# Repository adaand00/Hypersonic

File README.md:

# Hypersonic
Platform for audio development with ESP32-S3, Work in progress.

Design goals: 
Modularity. Flexibility. High Fidelity. 

Based on previous project: [Supersonic Quantumbox](https://github.com/GustavAbrahamsson/Supersonic-Quantumbox)

## Development progress:

### Hardware
- [x] ESP32-s3 + CODEC module ([`/Hypersonic_pcb`](./Hypersonic_pcb/))
- [x] Pedal with screen, potentiometers, and connetors. ([`/Hypersonic_pedal_pcb`](./Hypersonic_pedal_pcb/))
- [x] Assembled
- [ ] Fully tested

### Software
- [x] Peripheral drivers
- [ ] FreeRTOS system
- [ ] User interface

### Effects

- [x] Saturation (Overdrive/Fuzz)
- [x] VU meter
- [ ] Linear filters
- [ ] Compression
- [ ] Rotary speaker
- [ ] Wah-wah
- [ ] Echo/Reverb

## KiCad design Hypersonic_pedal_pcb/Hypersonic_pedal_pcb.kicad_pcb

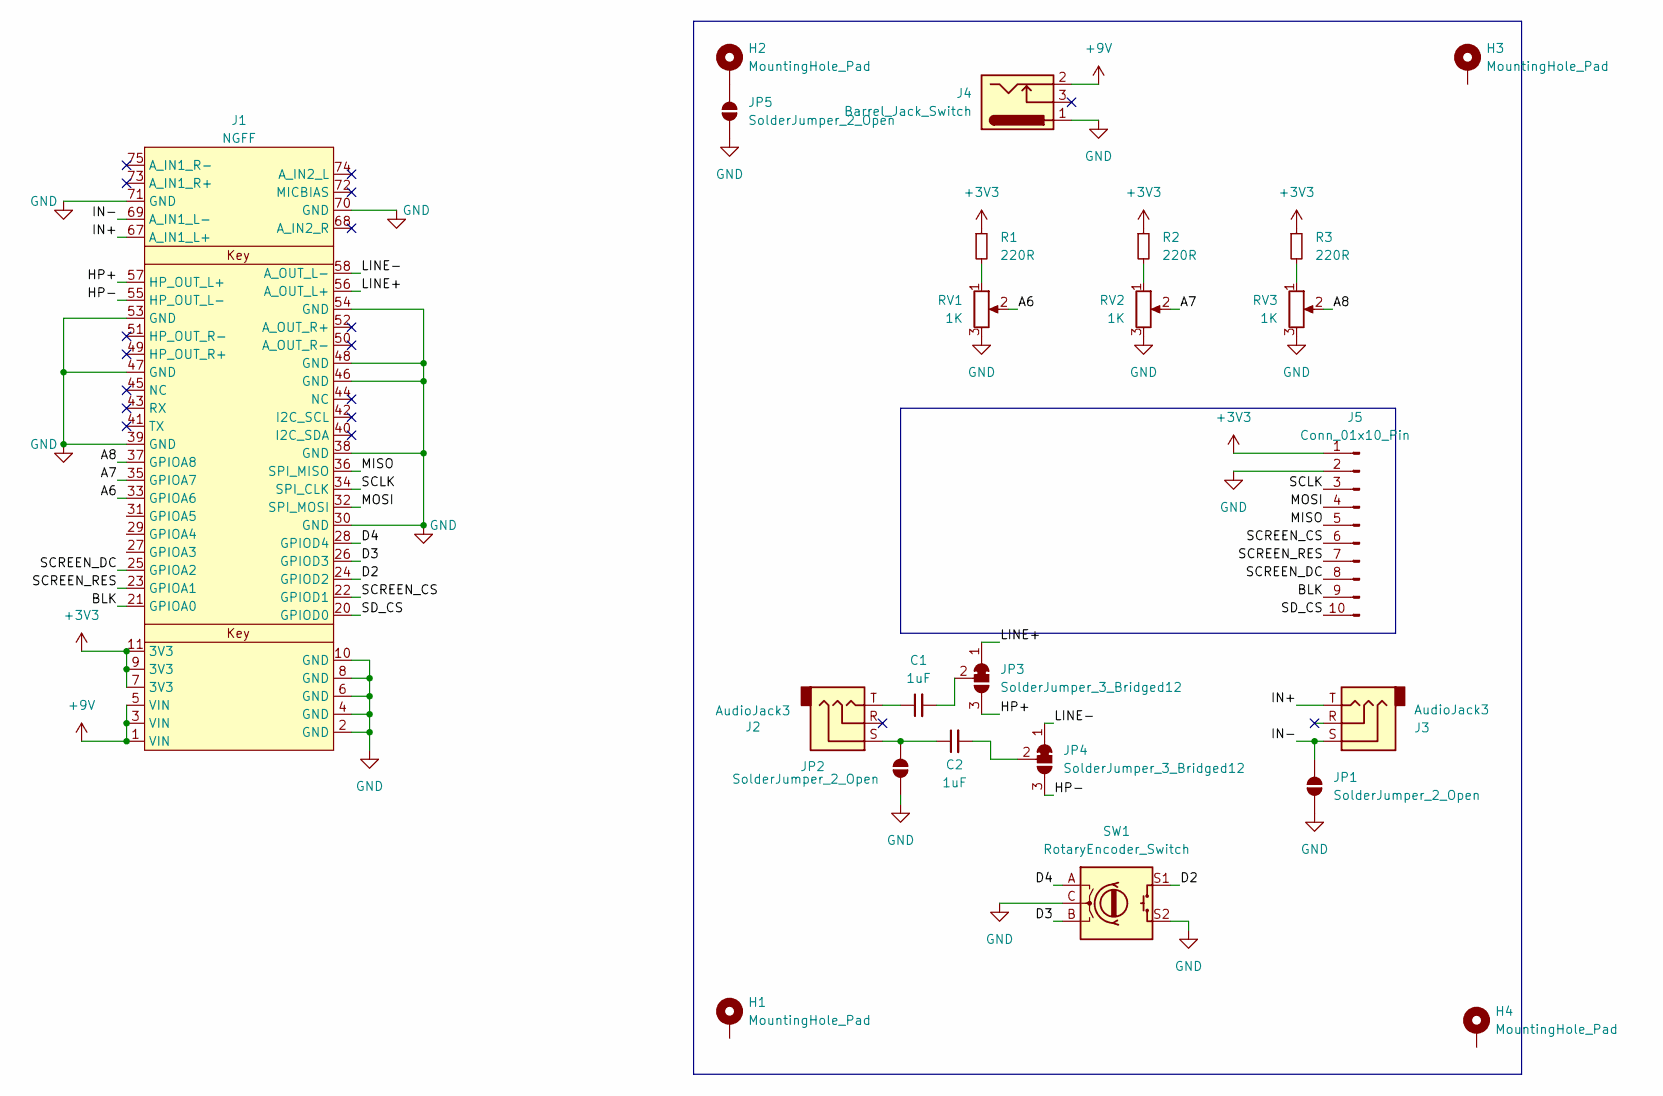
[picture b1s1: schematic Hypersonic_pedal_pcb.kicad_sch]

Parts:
C1, C2: 1uF; C_Rect_L18.0mm_W8.0mm_P15.00mm_FKS3_FKP3
H1, H2, H3, H4: MountingHole_Pad; MountingHole_2.2mm_M2_Pad_Via
J1: NGFF; TE_2199119-1
J2, J3: AudioJack3; Jack_6.35mm_Neutrik_NRJ6HF_Horizontal
J4: Barrel_Jack_Switch; BarrelJack_Horizontal
J5: Conn_01x10_Pin; DFROBOT_TFT_1_8
JP1, JP2, JP5: SolderJumper_2_Open; SolderJumper-2_P1.3mm_Open_TrianglePad1.0x1.5mm
JP3, JP4: SolderJumper_3_Bridged12; SolderJumper-3_P1.3mm_Bridged12_RoundedPad1.0x1.5mm
R1, R2, R3: 220R; R_0603_1608Metric
RV1, RV2, RV3: 1K; Potentiometer_Bourns_PTV09A-1_Single_Vertical
SW1: RotaryEncoder_Switch; RotaryEncoder_Bourns_Vertical_PEC12R-3x17F-Sxxxx

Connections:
+3V3: J1.7 (3V3), J1.9 (3V3), J1.11 (3V3), J5.1, R1.1, R2.1, R3.1
+9V: J1.1 (VIN), J1.3 (VIN), J1.5 (VIN), J4.2
/A6: J1.33 (GPIOA6), RV1.2
/A7: J1.35 (GPIOA7), RV2.2
/A8: J1.37 (GPIOA8), RV3.2
/BLK: J1.21 (GPIOA0), J5.9
/D2: J1.24 (GPIOD2), SW1.S1
/D3: J1.26 (GPIOD3), SW1.B
/D4: J1.28 (GPIOD4), SW1.A
/HP+: J1.57 (HP_OUT_L+), JP3.3 (B)
/HP-: J1.55 (HP_OUT_L-), JP4.3 (B)
/IN+: J1.67 (A_IN1_L+), J3.T
/IN-: J1.69 (A_IN1_L-), J3.S, JP1.2 (B)
/LINE+: J1.56 (A_OUT_L+), JP3.1 (A)
/LINE-: J1.58 (A_OUT_L-), JP4.1 (A)
/MISO: J1.36 (SPI_MISO), J5.5
/MOSI: J1.32 (SPI_MOSI), J5.4
/SCLK: J1.34 (SPI_CLK), J5.3
/SCREEN_CS: J1.22 (GPIOD1), J5.6
/SCREEN_DC: J1.25 (GPIOA2), J5.8
/SCREEN_RES: J1.23 (GPIOA1), J5.7
/SD_CS: J1.20 (GPIOD0), J5.10
GND: J1.2 (GND), J1.4 (GND), J1.6 (GND), J1.8 (GND), J1.10 (GND), J1.30 (GND), J1.38 (GND), J1.39 (GND), J1.46 (GND), J1.47 (GND), J1.48 (GND), J1.53 (GND), J1.54 (GND), J1.70 (GND), J1.71 (GND), J4.1, J5.2, JP1.1 (A), JP2.1 (A), JP5.1 (A), RV1.3, RV2.3, RV3.3, SW1.C, SW1.S2
unnamed: C1.1, J2.T
unnamed: C2.1, J2.S, JP2.2 (B)
unnamed: C1.2, JP3.2 (C)
unnamed: C2.2, JP4.2 (C)
unnamed: H2.1, JP5.2 (B)
unnamed: R1.2, RV1.1
unnamed: R2.2, RV2.1
unnamed: R3.2, RV3.1

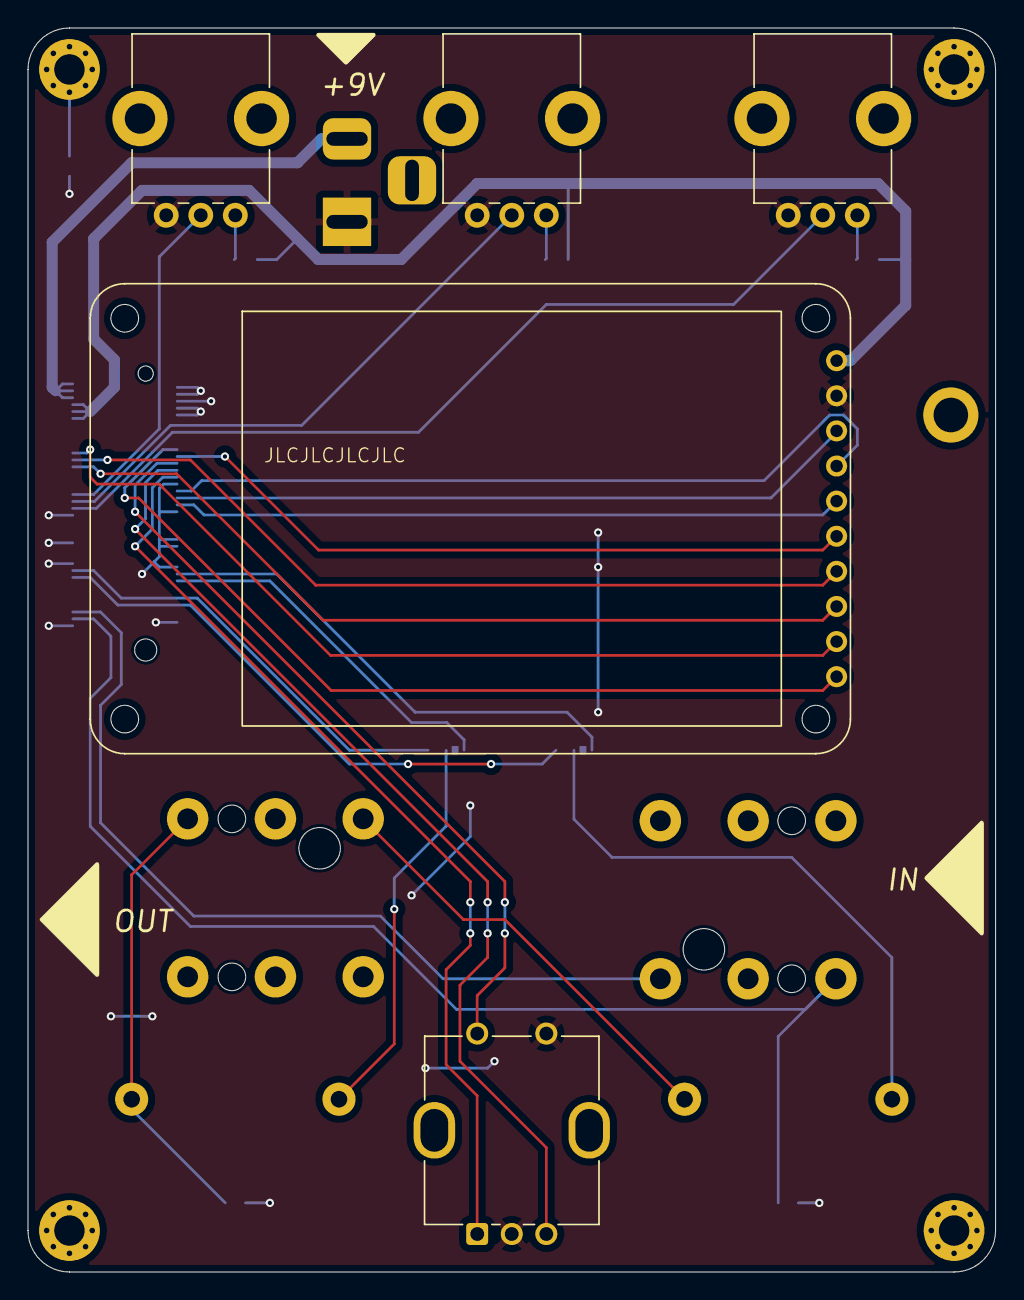
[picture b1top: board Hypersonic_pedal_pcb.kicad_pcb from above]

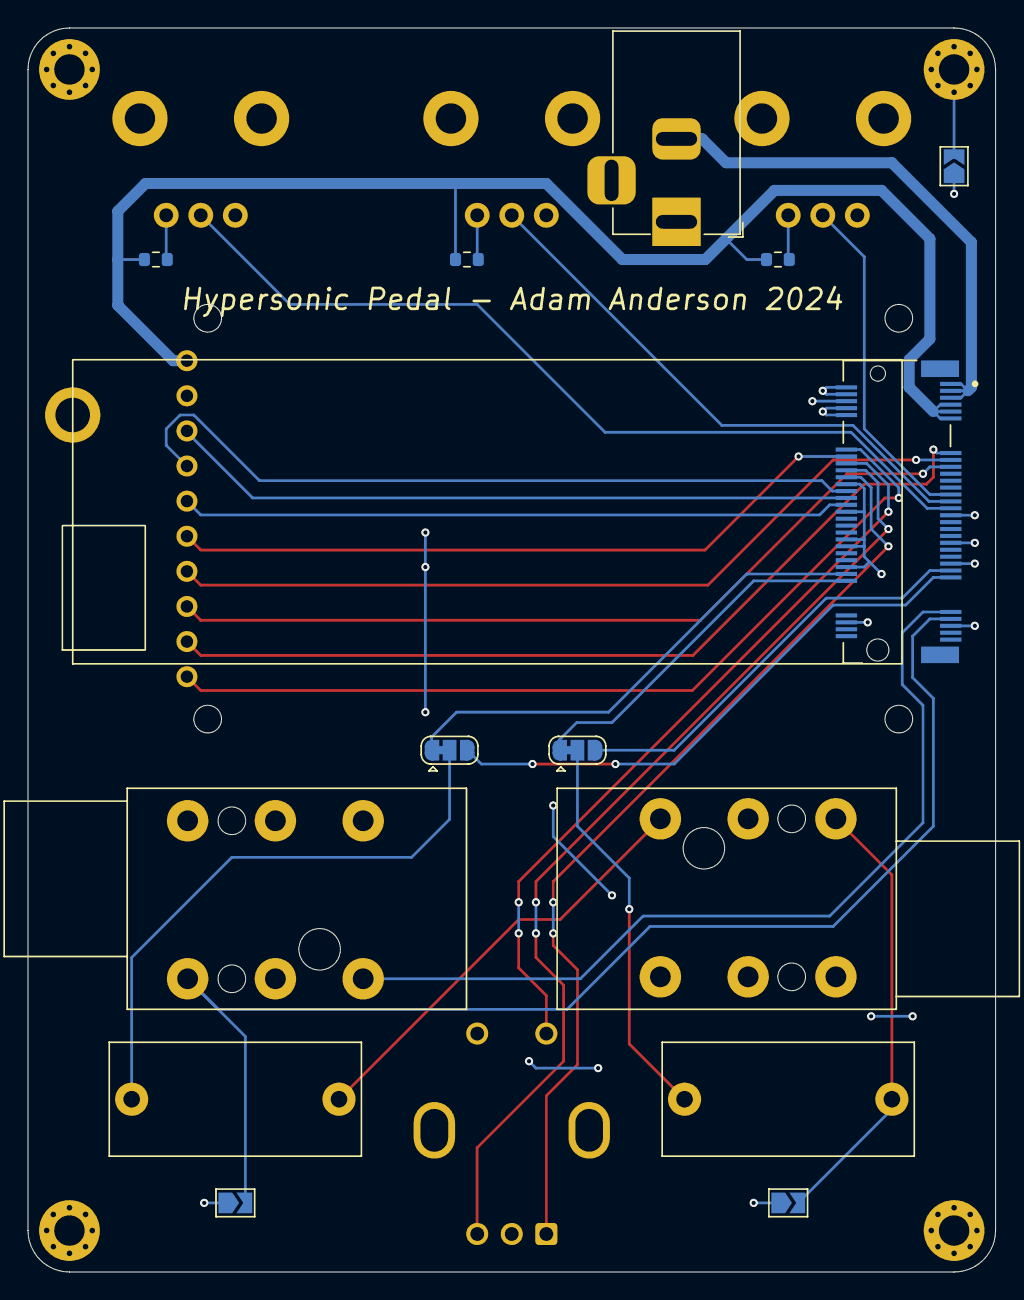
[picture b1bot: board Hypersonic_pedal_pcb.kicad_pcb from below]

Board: 2 copper layers, 70.0 x 90.0 mm, 23 parts (14 on the bottom side), 31 nets.

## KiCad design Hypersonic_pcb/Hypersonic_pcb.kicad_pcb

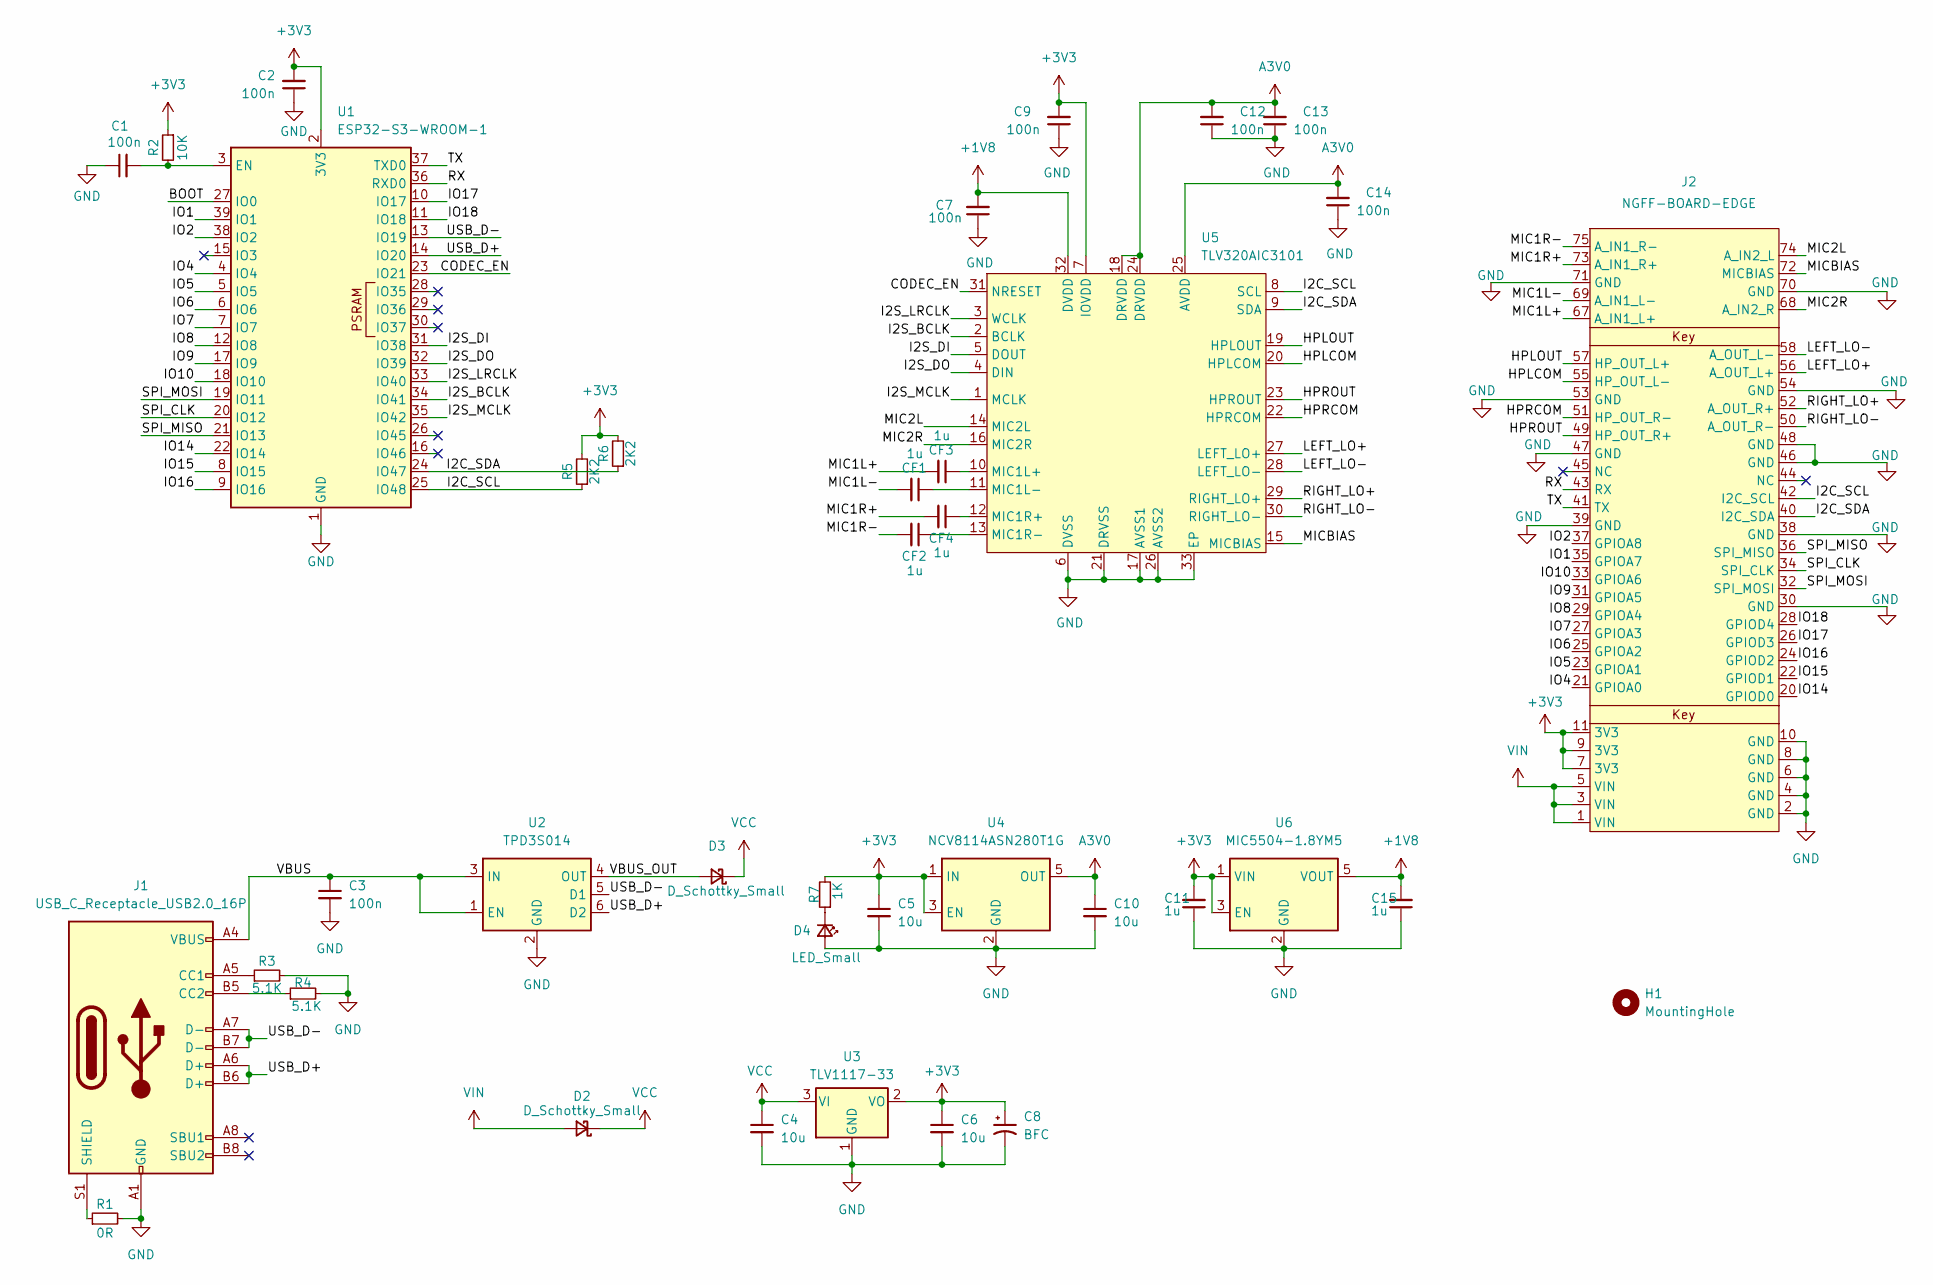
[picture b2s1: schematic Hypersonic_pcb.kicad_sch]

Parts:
C1, C2, C3, C7, C9, C12, C13, C14: 100n; C_0402_1005Metric
C4, C5, C6, C10: 10u; C_0805_2012Metric
C8: BFC; C_Elec_6.3x5.8
C11, C15: 1u; C_0603_1608Metric
CF1, CF2, CF3, CF4: 1u; C_1210_3225Metric
D2, D3: D_Schottky_Small; D_SOD-323_HandSoldering
D4: LED_Small; LED_0603_1608Metric
H1: MountingHole; MountingHole_2.2mm_M2
J1: USB_C_Receptacle_USB2.0_16P; USB_C_Receptacle_HRO_TYPE-C-31-M-12
J2: NGFF-BOARD-EDGE; NGFF_B+M
R1: 0R; R_0402_1005Metric
R2: 10K; R_0402_1005Metric
R3, R4: 5.1K; R_0402_1005Metric
R5, R6: 2K2; R_0402_1005Metric
R7: 1K; R_0402_1005Metric
U1: ESP32-S3-WROOM-1; ESP32-S3-WROOM-1U
U2: TPD3S014; SOT-23-6
U3: TLV1117-33; SOT-223-3_TabPin2
U4: NCV8114ASN280T1G; TSOT-23-5
U5: TLV320AIC3101; QFN-32-1EP_5x5mm_P0.5mm_EP3.45x3.45mm
U6: MIC5504-1.8YM5; SOT-23-5

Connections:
+1V8: C7.2, C15.2, U5.32 (DVDD), U6.5 (VOUT)
+3V3: C2.2, C5.1, C6.1, C8.1, C9.2, C11.2, J2.7 (3V3), J2.9 (3V3), J2.11 (3V3), R2.1, R5.2, R6.2, R7.2, U1.2 (3V3), U3.2 (VO), U4.1 (IN), U4.3 (EN), U5.7 (IOVDD), U6.1 (VIN), U6.3 (EN)
/BOOT: U1.27 (IO0)
/CODEC_EN: U1.23 (IO21), U5.31 (NRESET)
/HPLCOM: J2.55 (HP_OUT_L-), U5.20 (HPLCOM)
/HPLOUT: J2.57 (HP_OUT_L+), U5.19 (HPLOUT)
/HPRCOM: J2.51 (HP_OUT_R-), U5.22 (HPRCOM)
/HPROUT: J2.49 (HP_OUT_R+), U5.23 (HPROUT)
/I2C_SCL: J2.42 (I2C_SCL), R5.1, U1.25 (IO48), U5.8 (SCL)
/I2C_SDA: J2.40 (I2C_SDA), R6.1, U1.24 (IO47), U5.9 (SDA)
/I2S_BCLK: U1.34 (IO41), U5.2 (BCLK)
/I2S_DI: U1.31 (IO38), U5.5 (DOUT)
/I2S_DO: U1.32 (IO39), U5.4 (DIN)
/I2S_LRCLK: U1.33 (IO40), U5.3 (WCLK)
/I2S_MCLK: U1.35 (IO42), U5.1 (MCLK)
/IO1: J2.35 (GPIOA7), U1.39 (IO1)
/IO2: J2.37 (GPIOA8), U1.38 (IO2)
/IO4: J2.21 (GPIOA0), U1.4 (IO4)
/IO5: J2.23 (GPIOA1), U1.5 (IO5)
/IO6: J2.25 (GPIOA2), U1.6 (IO6)
/IO7: J2.27 (GPIOA3), U1.7 (IO7)
/IO8: J2.29 (GPIOA4), U1.12 (IO8)
/IO9: J2.31 (GPIOA5), U1.17 (IO9)
/IO10: J2.33 (GPIOA6), U1.18 (IO10)
/IO14: J2.20 (GPIOD0), U1.22 (IO14)
/IO15: J2.22 (GPIOD1), U1.8 (IO15)
/IO16: J2.24 (GPIOD2), U1.9 (IO16)
/IO17: J2.26 (GPIOD3), U1.10 (IO17)
/IO18: J2.28 (GPIOD4), U1.11 (IO18)
/LEFT_LO+: J2.56 (A_OUT_L+), U5.27 (LEFT_LO+)
/LEFT_LO-: J2.58 (A_OUT_L-), U5.28 (LEFT_LO-)
/MIC1L+: CF3.2, J2.67 (A_IN1_L+)
/MIC1L-: CF1.2, J2.69 (A_IN1_L-)
/MIC1R+: CF4.2, J2.73 (A_IN1_R+)
/MIC1R-: CF2.2, J2.75 (A_IN1_R-)
/MIC2L: J2.74 (A_IN2_L), U5.14 (MIC2L)
/MIC2R: J2.68 (A_IN2_R), U5.16 (MIC2R)
/MICBIAS: J2.72 (MICBIAS), U5.15 (MICBIAS)
/RIGHT_LO+: J2.52 (A_OUT_R+), U5.29 (RIGHT_LO+)
/RIGHT_LO-: J2.50 (A_OUT_R-), U5.30 (RIGHT_LO-)
/RX: J2.43 (RX), U1.36 (RXD0)
/SPI_CLK: J2.34 (SPI_CLK), U1.20 (IO12)
/SPI_MISO: J2.36 (SPI_MISO), U1.21 (IO13)
/SPI_MOSI: J2.32 (SPI_MOSI), U1.19 (IO11)
/TX: J2.41 (TX), U1.37 (TXD0)
/USB_D+: J1.A6 (D+), J1.B6 (D+), U1.14 (IO20), U2.6 (D2)
/USB_D-: J1.A7 (D-), J1.B7 (D-), U1.13 (IO19), U2.5 (D1)
/VBUS: C3.1, J1.A4 (VBUS), J1.A9 (VBUS), J1.B4 (VBUS), J1.B9 (VBUS), U2.1 (EN), U2.3 (IN)
/VBUS_OUT: D3.2 (A), U2.4 (OUT)
A3V0: C10.1, C12.2, C13.2, C14.2, U4.5 (OUT), U5.18 (DRVDD), U5.24 (DRVDD), U5.25 (AVDD)
GND: C1.1, C2.1, C3.2, C4.2, C5.2, C6.2, C7.1, C8.2, C9.1, C10.2, C11.1, C12.1, C13.1, C14.1, C15.1, D4.2 (A), J1.A1 (GND), J1.A12 (GND), J1.B1 (GND), J1.B12 (GND), J2.2 (GND), J2.4 (GND), J2.6 (GND), J2.8 (GND), J2.10 (GND), J2.30 (GND), J2.38 (GND), J2.39 (GND), J2.46 (GND), J2.47 (GND), J2.48 (GND), J2.53 (GND), J2.54 (GND), J2.70 (GND), J2.71 (GND), R1.2, R3.2, R4.2, U1.1 (GND), U1.40 (GND), U1.41 (GND), U2.2 (GND), U3.1 (GND), U4.2 (GND), U5.6 (DVSS), U5.17 (AVSS1), U5.21 (DRVSS), U5.26 (AVSS2), U5.33 (EP), U6.2 (GND)
unnamed: D4.1 (K), R7.1
unnamed: J1.A5 (CC1), R3.1
unnamed: J1.B5 (CC2), R4.1
unnamed: J1.S1 (SHIELD), R1.1
unnamed: C1.2, R2.2, U1.3 (EN)
unnamed: CF3.1, U5.10 (MIC1L+)
unnamed: CF1.1, U5.11 (MIC1L-)
unnamed: CF4.1, U5.12 (MIC1R+)
unnamed: CF2.1, U5.13 (MIC1R-)
VCC: C4.1, D2.1 (K), D3.1 (K), U3.3 (VI)
VIN: D2.2 (A), J2.1 (VIN), J2.3 (VIN), J2.5 (VIN)

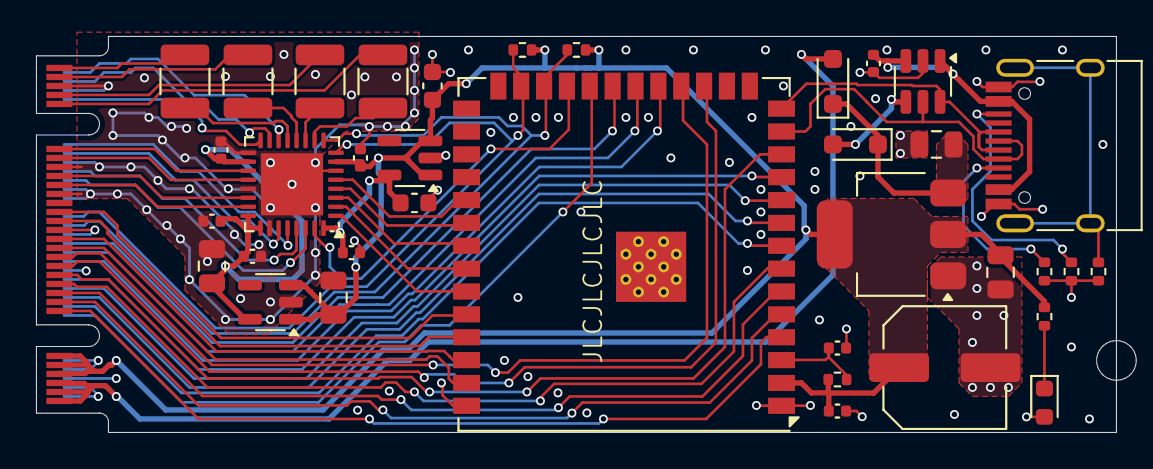
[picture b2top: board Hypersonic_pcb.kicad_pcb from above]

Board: 4 copper layers, 60.0 x 22.0 mm, 38 parts (0 on the bottom side), 61 nets.

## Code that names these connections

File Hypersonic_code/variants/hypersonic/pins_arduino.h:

#ifndef Pins_Arduino_h
#define Pins_Arduino_h

#include <stdint.h>

#define USB_VID          0x303a
#define USB_PID          0x814D  // for user apps (https://github.com/espressif/usb-pids/pull/77)
#define USB_MANUFACTURER "Adam"
#define USB_PRODUCT      "Hypersonic"
#define USB_SERIAL       ""

// ADC enabled
static const uint8_t A0 = 4;
static const uint8_t A1 = 5;
static const uint8_t A2 = 6;
static const uint8_t A3 = 7;
static const uint8_t A4 = 8;
static const uint8_t A5 = 9;
static const uint8_t A6 = 10;
static const uint8_t A7 = 1;
static const uint8_t A8 = 2;

// No ADC
static const uint8_t D0 = 14;
static const uint8_t D1 = 15;
static const uint8_t D2 = 16;
static const uint8_t D3 = 17;
static const uint8_t D4 = 18;

// SPI
static const uint8_t MISO = 13;
static const uint8_t MOSI = 11;
static const uint8_t SCK  = 12;

static const uint8_t SS   = 10;

// I2C (Pull-ups on board)
static const uint8_t SDA  = 47;
static const uint8_t SCL  = 48;

// Codec pins
static const uint8_t I2S_DI   = 38;
static const uint8_t I2S_DO   = 39;
static const uint8_t I2S_WCLK = 40;
static const uint8_t I2S_BCLK = 41;
static const uint8_t I2S_MCLK = 42;
static const uint8_t CODEC_EN = 21;

// UART
static const uint8_t TX = 43;
static const uint8_t RX = 44;

#endif /* Pins_Arduino_h */

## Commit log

2024-05-05 Hello World!
2024-05-05 Add custom pin definitions
2024-05-10 Peripherals working
2024-05-15 Add effects
2024-05-29 Docs
2024-05-29 Work on effects
